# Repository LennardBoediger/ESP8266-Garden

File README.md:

The idea is that the plant will be watered daily at a certain Time for a certain duration, which can be set via the Web interface.

## Hardware
- esp8266-v03  
- [Water Pump](http://www.ebay.de/itm/Mini-Micro-Tauchmotorpumpe-Wasserpumpen-Aquarium-Tauchpumpe-DC-2-5-6V-120-L-H-/272392089268?hash=item3f6bd56eb4:g:RyMAAOSw8w1X6kNP)  
- Water Reservoir  
- Plastic Tubing  
-  Status LED's

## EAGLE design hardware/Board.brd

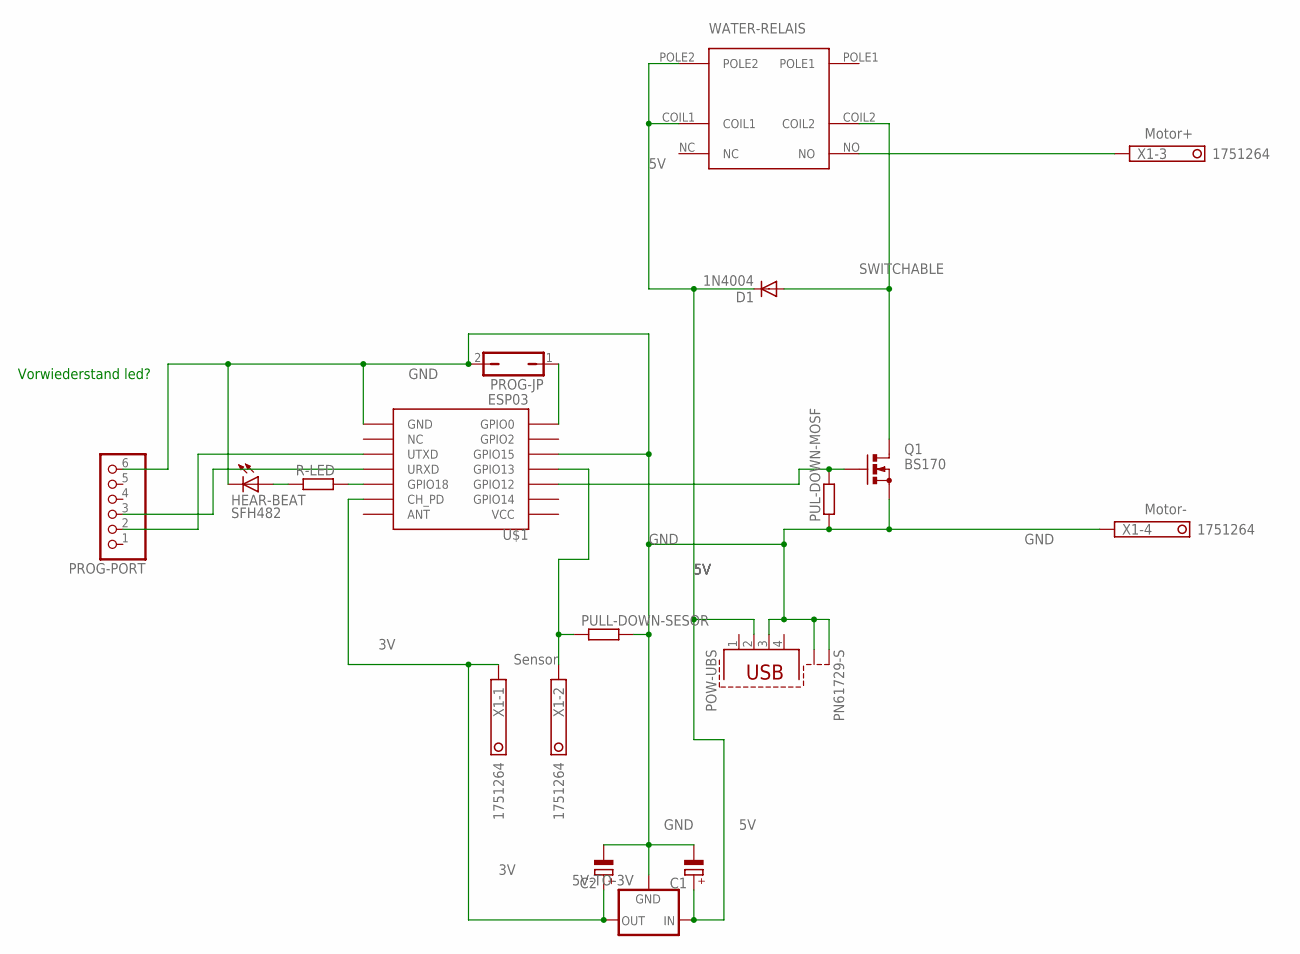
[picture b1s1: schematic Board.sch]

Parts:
5V-TO-3V: 78XXL
C1, C2: CPOL-EUE2.5-6; E2,5-6
D1: 1N4004; DO41-10
HEAR-BEAT: SFH482
POW-UBS: PN61729-S
PROG-JP: JP1Q; JP1
PROG-PORT: PINHD-1X6; 1X06
PUL-DOWN-MOSF: R-EU_0207/10; 0207/10
PULL-DOWN-SESOR: R-EU_0207/10; 0207/10
Q1: BS170; SOT54E
R-LED: R-EU_0207/10; 0207/10
U$1: ESP03
WATER-RELAIS: HJR-4102-L-C; HJR-4102-L
X1: 1751264

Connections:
3V: 5V-TO-3V.OUT, C2.+, U$1.CH_PD, X1.1
5V: 5V-TO-3V.IN, C1.+, D1.C, POW-UBS.2, WATER-RELAIS.COIL1, WATER-RELAIS.POLE2
GND: 5V-TO-3V.GND, C1.-, C2.-, HEAR-BEAT.K (C), POW-UBS.3, POW-UBS.S1, POW-UBS.S2, PROG-JP.2, PROG-PORT.6, PUL-DOWN-MOSF.1, PULL-DOWN-SESOR.2, Q1.S, U$1.GND, U$1.GPIO15, X1.4
unnamed: PUL-DOWN-MOSF.2, Q1.G, U$1.GPIO12
unnamed: PROG-PORT.3, U$1.URXD
unnamed: HEAR-BEAT.A, R-LED.1
unnamed: WATER-RELAIS.NO, X1.3
unnamed: PROG-PORT.2, U$1.UTXD
unnamed: R-LED.2, U$1.GPIO18
unnamed: PROG-JP.1, U$1.GPIO0
unnamed: PULL-DOWN-SESOR.1, U$1.GPIO13, X1.2
SWITCHABLE: D1.A, Q1.D, WATER-RELAIS.COIL2

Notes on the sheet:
Vorwiederstand led?
Motor+
Motor-
Sensor

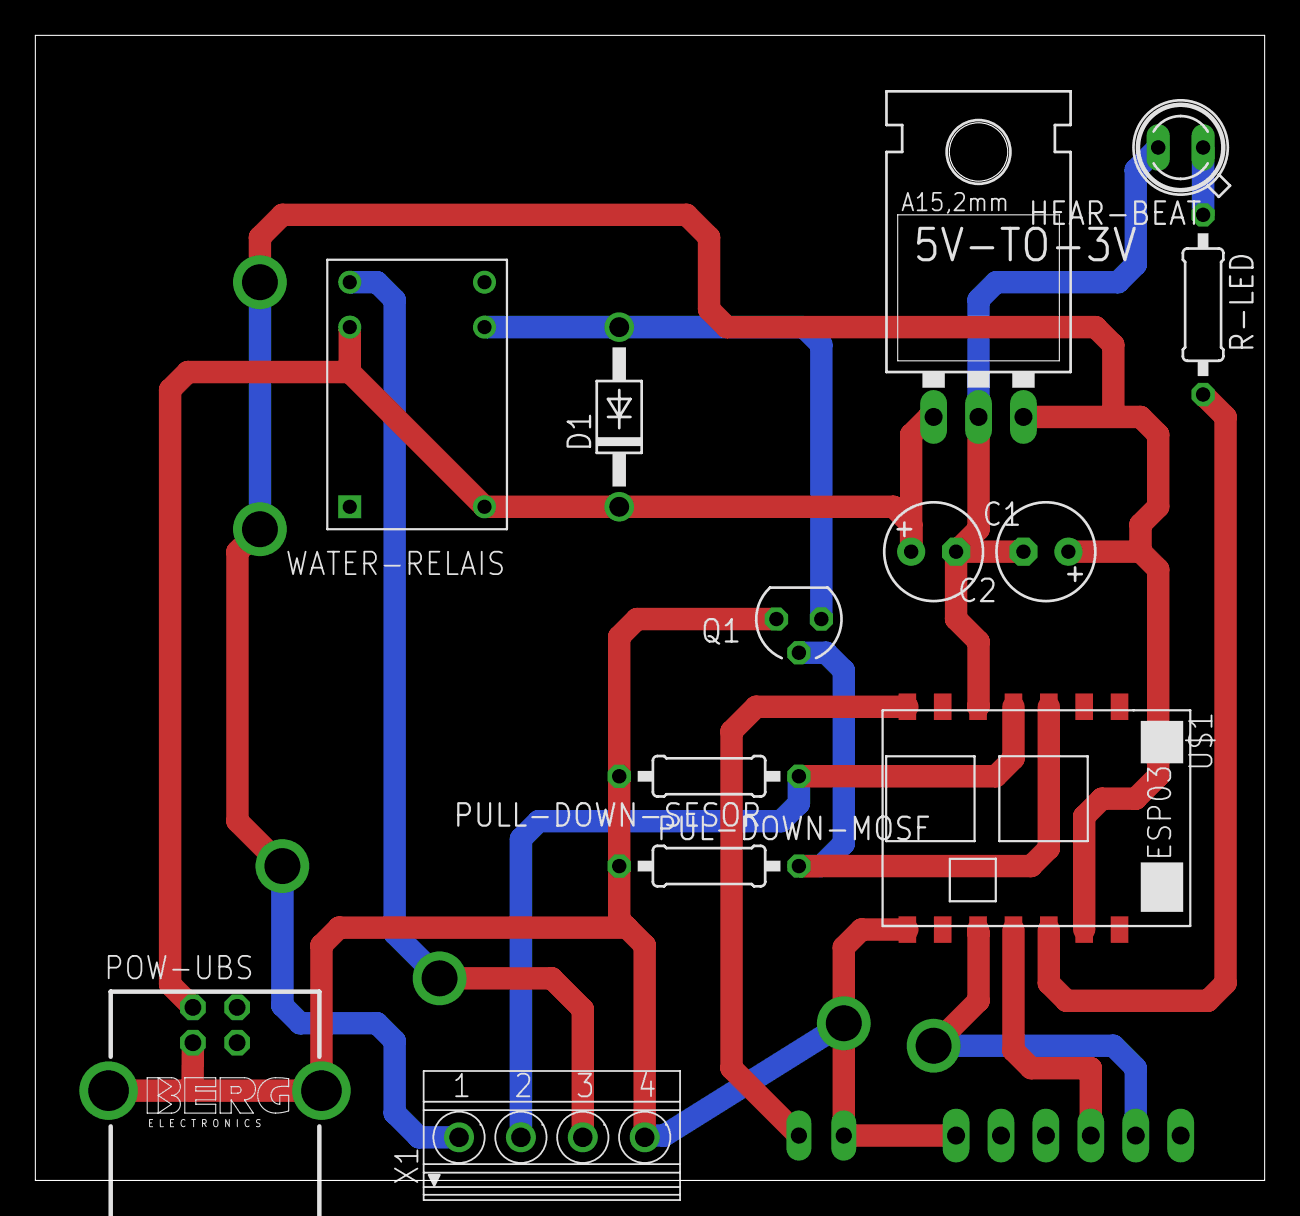
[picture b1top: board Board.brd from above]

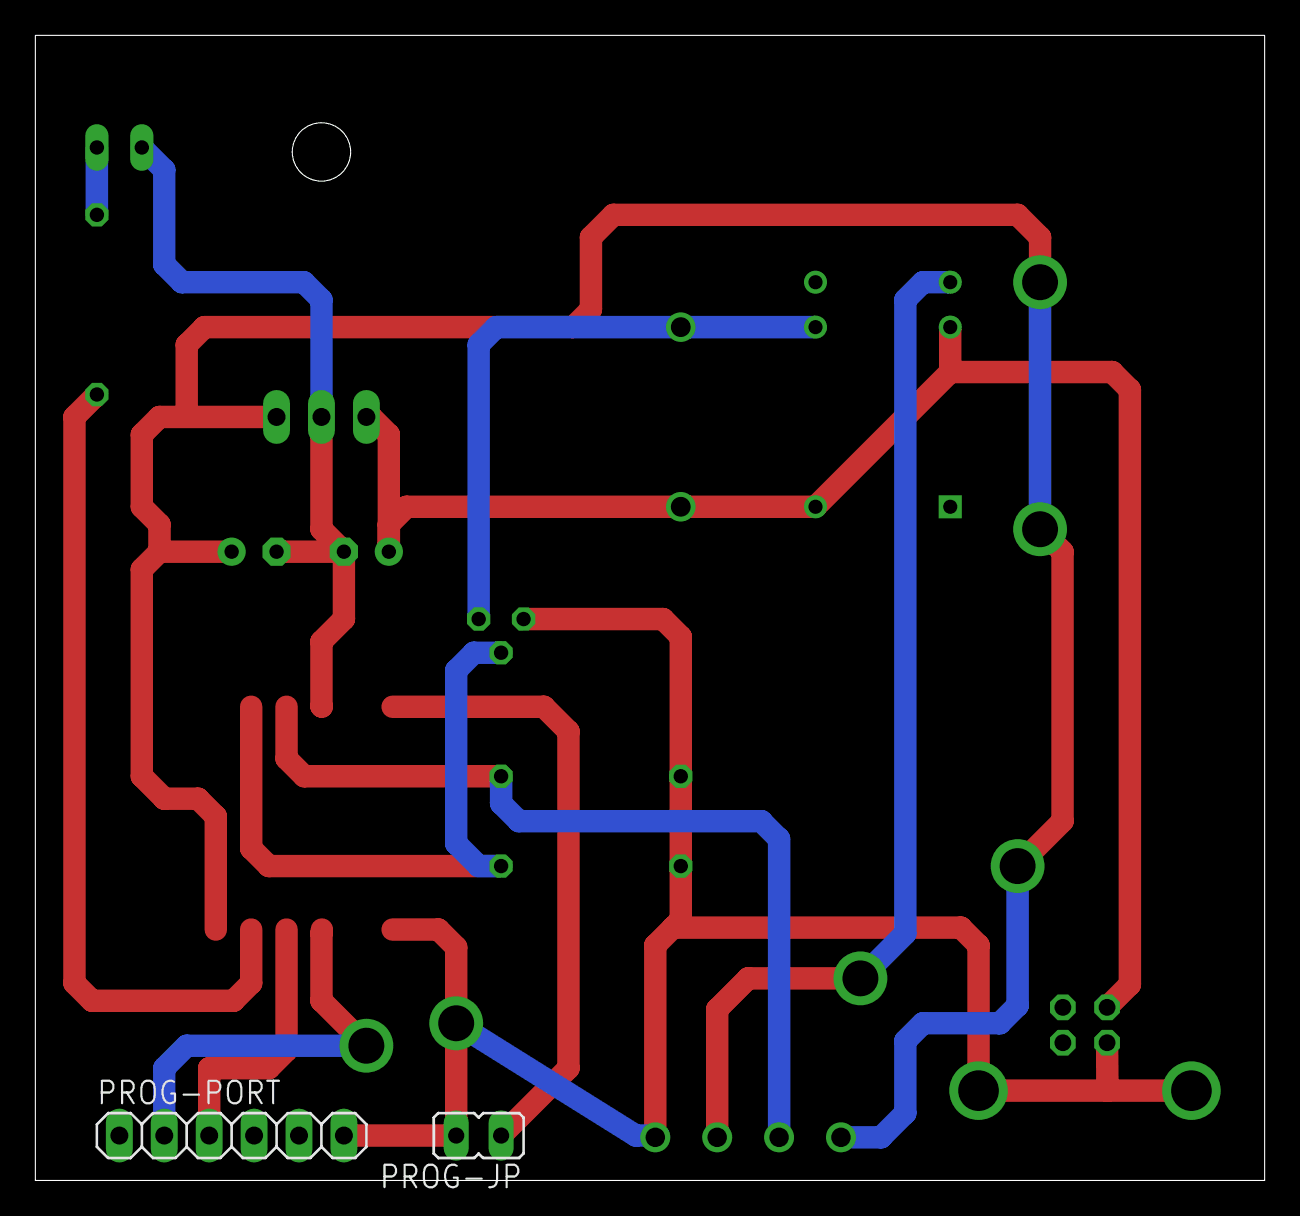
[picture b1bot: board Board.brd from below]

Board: 2 copper layers, 69.5 x 64.8 mm, 15 parts (2 on the bottom side), 12 nets.

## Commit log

2016-10-27 changes to readme
2016-10-27 changes to .gitcommit
2016-10-28 add bootstrap
2016-10-30 nothing to see here
2021-01-04 rename folder
2021-01-04 clean up
2021-01-19 add PCB
